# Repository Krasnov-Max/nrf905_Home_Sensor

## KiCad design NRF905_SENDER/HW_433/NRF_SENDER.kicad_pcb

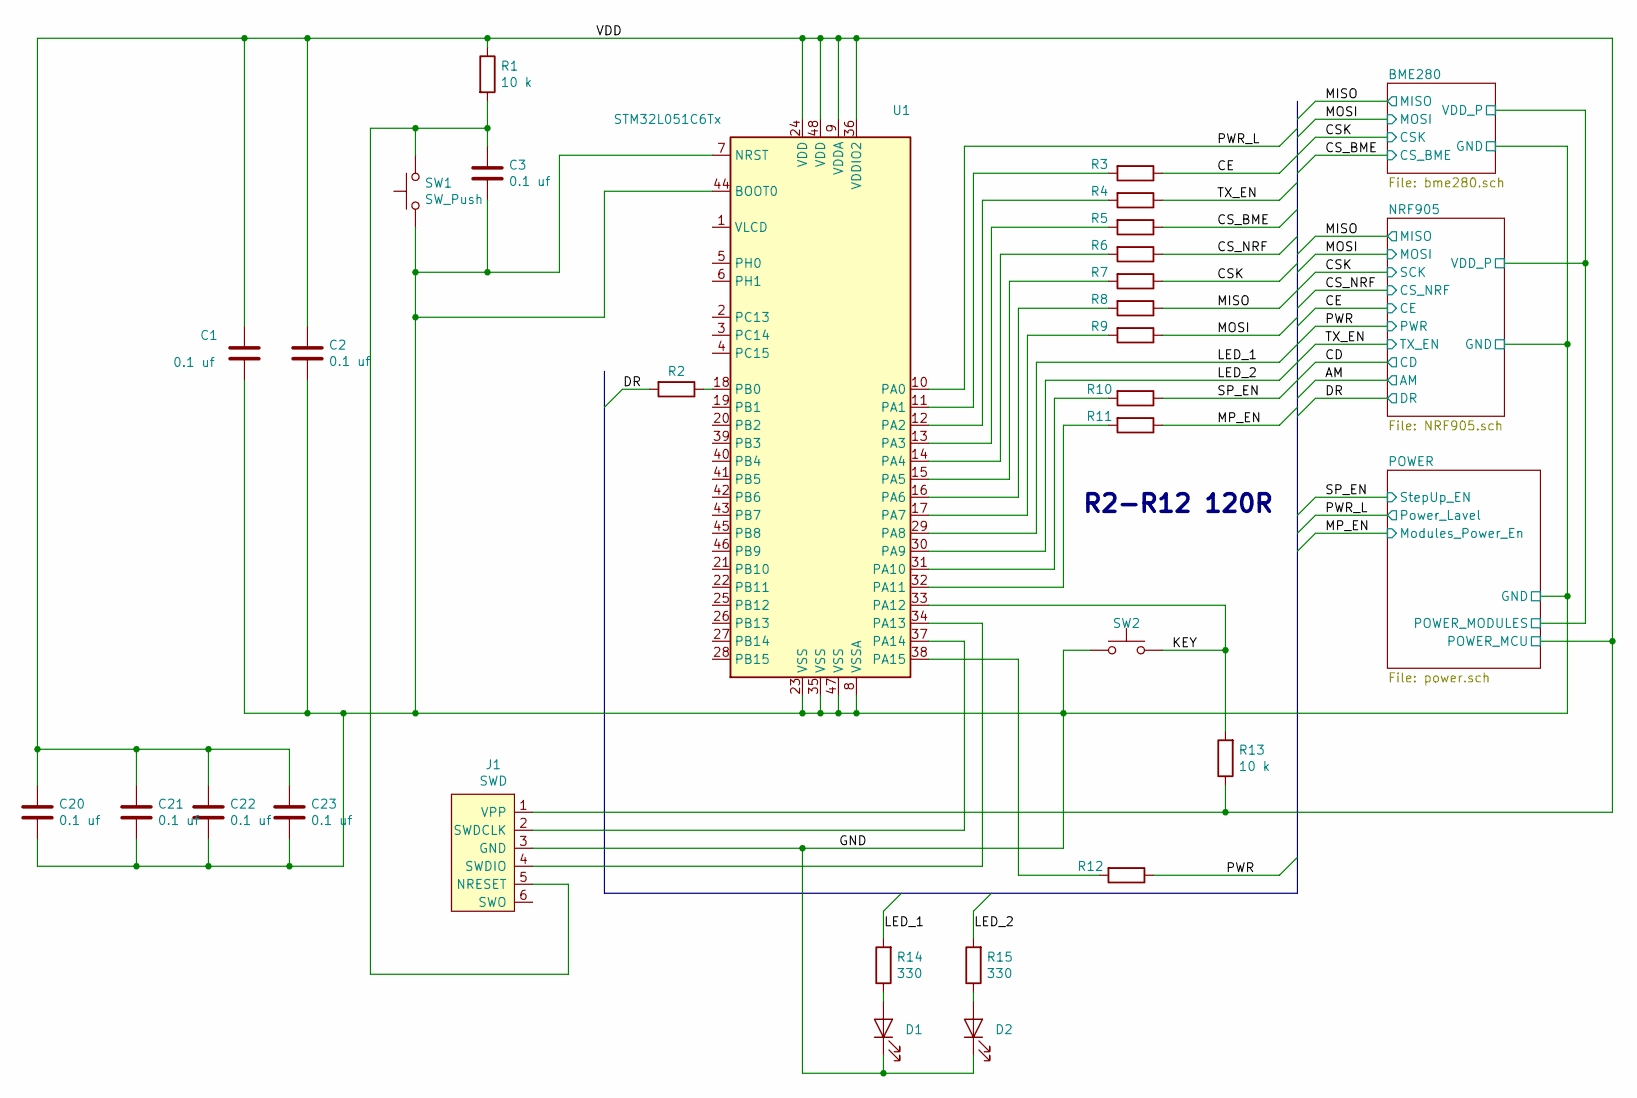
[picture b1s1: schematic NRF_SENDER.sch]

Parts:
C1, C2, C3, C20, C21, C22, C23: 0.1 uf; C_0603_1608Metric_Pad1.05x0.95mm_HandSolder
D1, D2: LED; LED_0603_1608Metric_Pad1.05x0.95mm_HandSolder
J1: SWD; PinHeader_1x06_P2.54mm_Vertical
R1, R13: 10 k; R_0603_1608Metric_Pad1.05x0.95mm_HandSolder
R2, R3, R4, R5, R6, R7, R8, R9, R10, R11, R12: 120; R_0603_1608Metric_Pad1.05x0.95mm_HandSolder
R14, R15: 330; R_0603_1608Metric_Pad1.05x0.95mm_HandSolder
SW1, SW2: SW_Push; SW_SPST_EVQP2
U1: STM32L051C6Tx; LQFP-48_7x7mm_P0.5mm

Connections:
/CE: R3.1; also elsewhere on the board
/CSK: R7.1; also elsewhere on the board
/CS_BME: R5.1; also elsewhere on the board
/CS_NRF: R6.1; also elsewhere on the board
/DR: R2.2; also elsewhere on the board
/KEY: R13.2, SW2.2, U1.33 (PA12)
/LED_1: R14.2, U1.29 (PA8)
/LED_2: R15.2, U1.30 (PA9)
/MISO: R8.1; also elsewhere on the board
/MOSI: R9.1; also elsewhere on the board
/MP_EN: R11.1; also elsewhere on the board
/PWR: R12.1; also elsewhere on the board
/PWR_L: U1.10 (PA0); also elsewhere on the board
/SP_EN: R10.1; also elsewhere on the board
/TX_EN: R4.1; also elsewhere on the board
/VDD: C1.1, C2.1, C20.1, C21.1, C22.1, C23.1, J1.1 (VPP), R1.1, R13.1, U1.9 (VDDA), U1.24 (VDD), U1.36 (VDDIO2), U1.48 (VDD); also elsewhere on the board
GND: C1.2, C2.2, C3.2, C20.2, C21.2, C22.2, C23.2, D1.1 (K), D2.1 (K), J1.3 (GND), SW1.1, SW2.1, U1.7 (NRST), U1.8 (VSSA), U1.23 (VSS), U1.35 (VSS), U1.44 (BOOT0), U1.47 (VSS); also elsewhere on the board
unnamed: C3.1, J1.5 (NRESET), R1.2, SW1.2
unnamed: D1.2 (A), R14.1
unnamed: D2.2 (A), R15.1
unnamed: J1.2 (SWDCLK), U1.37 (PA14)
unnamed: J1.4 (SWDIO), U1.34 (PA13)
unnamed: R2.1, U1.18 (PB0)
unnamed: R3.2, U1.11 (PA1)
unnamed: R4.2, U1.12 (PA2)
unnamed: R5.2, U1.13 (PA3)
unnamed: R6.2, U1.14 (PA4)
unnamed: R7.2, U1.15 (PA5)
unnamed: R8.2, U1.16 (PA6)
unnamed: R9.2, U1.17 (PA7)
unnamed: R10.2, U1.31 (PA10)
unnamed: R11.2, U1.32 (PA11)
unnamed: R12.2, U1.38 (PA15)

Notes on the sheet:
R2-R12 120R

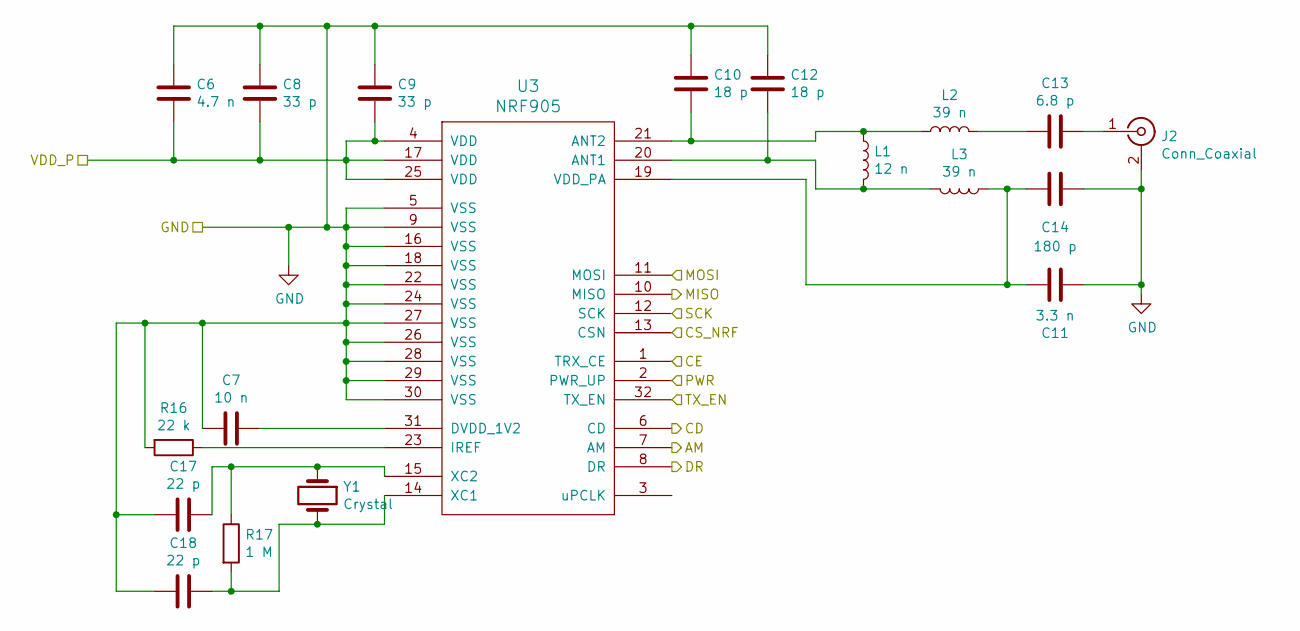
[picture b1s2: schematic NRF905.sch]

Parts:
C6: 4.7 n; C_0402_1005Metric
C7: 10 n; C_0402_1005Metric
C8, C9: 33 p; C_0402_1005Metric
C10, C12: 18 p; C_0402_1005Metric
C11: 3.3 n; C_0402_1005Metric
C13: 6.8 p; C_0402_1005Metric
C14: 180 p; C_0402_1005Metric
C17, C18: 22 p; C_0402_1005Metric
J2: Conn_Coaxial; U.FL_Molex_MCRF_73412-0110_Vertical
L1: 12 n; L_0402_1005Metric
L2, L3: 39 n; L_0402_1005Metric
R16: 22 k; R_0603_1608Metric_Pad1.05x0.95mm_HandSolder
R17: 1 M; R_0402_1005Metric
U3: NRF905; QFN-32-1EP_5x5mm_P0.5mm_EP3.6x3.6mm
Y1: Crystal; Crystal_SMD_TXC_7A-2Pin_5x3.2mm

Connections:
/CE: U3.1 (TRX_CE); also elsewhere on the board
/CSK: U3.12 (SCK); also elsewhere on the board
/CS_NRF: U3.13 (CSN); also elsewhere on the board
/DR: U3.8 (DR); also elsewhere on the board
/MISO: U3.10 (MISO); also elsewhere on the board
/MOSI: U3.11 (MOSI); also elsewhere on the board
/POWER/POWER_MODULES: C6.2, C8.2, C9.2, U3.4 (VDD), U3.17 (VDD), U3.25 (VDD); also elsewhere on the board
/PWR: U3.2 (PWR_UP); also elsewhere on the board
/TX_EN: U3.32 (TX_EN); also elsewhere on the board
GND: C6.1, C7.2, C8.1, C9.1, C10.1, C11.2, C12.1, C14.1, C17.2, C18.2, J2.2 (Ext), R16.2, U3.5 (VSS), U3.9 (VSS), U3.16 (VSS), U3.18 (VSS), U3.22 (VSS), U3.24 (VSS), U3.26 (VSS), U3.27 (VSS), U3.28 (VSS), U3.29 (VSS), U3.30 (VSS), U3.33; also elsewhere on the board
unnamed: C7.1, U3.31 (DVDD_1V2)
unnamed: C10.2, L1.1, L2.1, U3.21 (ANT2)
unnamed: C11.1, C14.2, L3.1, U3.19 (VDD_PA)
unnamed: C12.2, L1.2, L3.2, U3.20 (ANT1)
unnamed: C13.1, J2.1 (In)
unnamed: C13.2, L2.2
unnamed: C17.1, R17.1, U3.15 (XC2), Y1.1
unnamed: C18.1, R17.2, U3.14 (XC1), Y1.2
unnamed: R16.1, U3.23 (IREF)

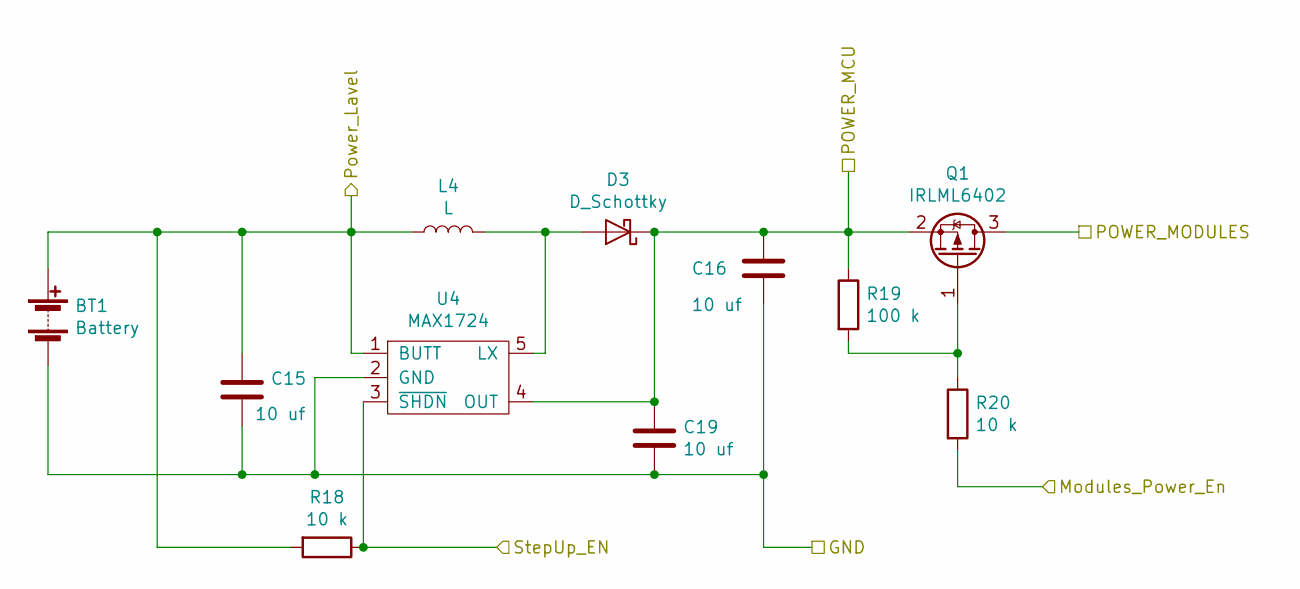
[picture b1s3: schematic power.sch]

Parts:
BT1: Battery; CR14250
C15, C16, C19: 10 uf; C_0603_1608Metric
D3: D_Schottky; D_SOD-123F
L4: L; L_Bourns-SRN8040_8x8.15mm
Q1: IRLML6402; SOT-23
R18, R20: 10 k; R_0603_1608Metric_Pad1.05x0.95mm_HandSolder
R19: 100 k; R_0603_1608Metric_Pad1.05x0.95mm_HandSolder
U4: MAX1724; TSOT

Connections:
/MP_EN: R20.2; also elsewhere on the board
/POWER/POWER_MODULES: Q1.3 (D); also elsewhere on the board
/PWR_L: BT1.1 (+), C15.1, L4.1, R18.2, U4.1 (BUTT); also elsewhere on the board
/SP_EN: R18.1, U4.3 (~SHDN); also elsewhere on the board
/VDD: C16.1, C19.1, D3.1 (K), Q1.2 (S), R19.1, U4.4 (OUT); also elsewhere on the board
GND: BT1.2 (-), C15.2, C16.2, C19.2, U4.2 (GND); also elsewhere on the board
unnamed: D3.2 (A), L4.2, U4.5 (LX)
unnamed: Q1.1 (G), R19.2, R20.1

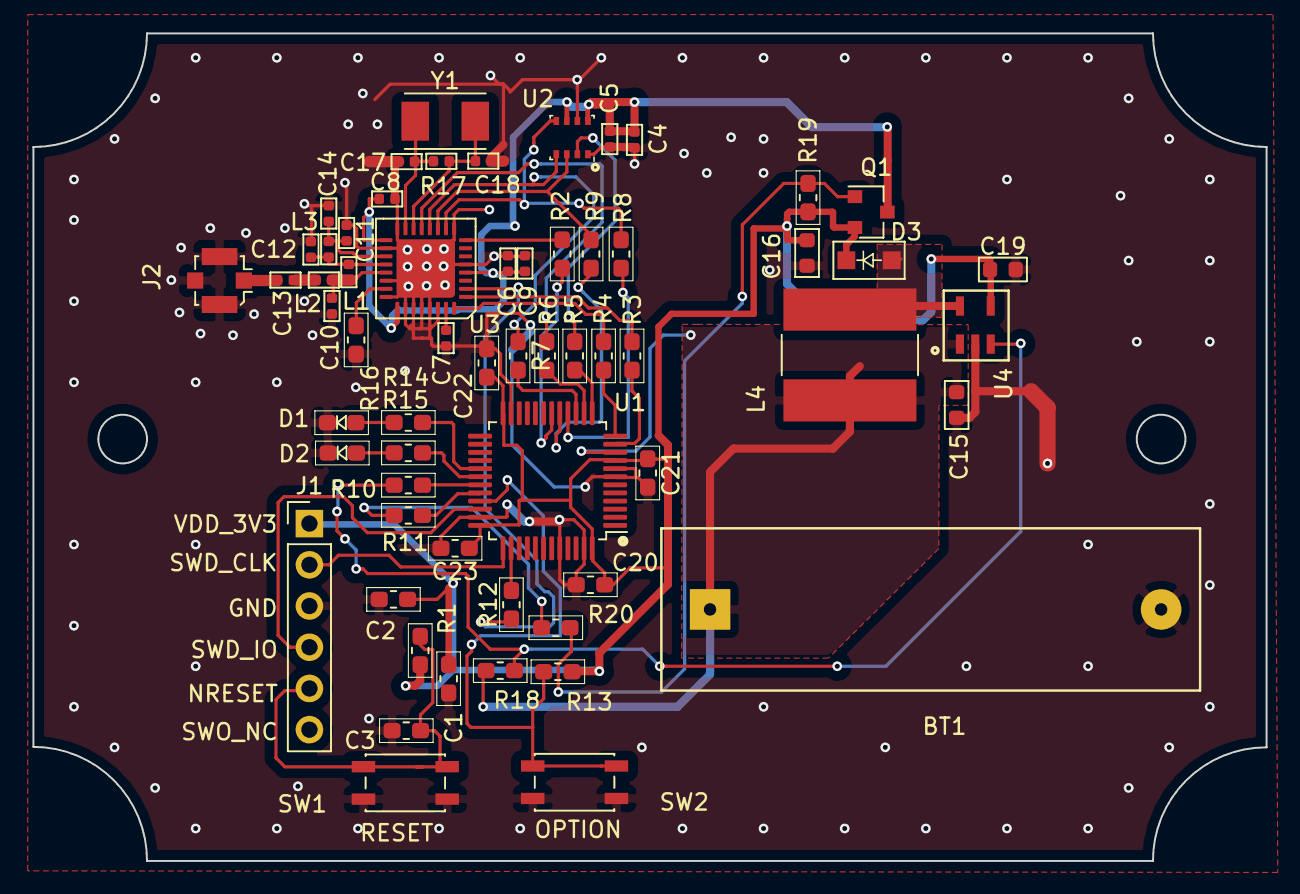
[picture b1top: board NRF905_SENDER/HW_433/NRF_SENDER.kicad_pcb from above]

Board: 2 copper layers, 76.0 x 51.0 mm, 61 parts (0 on the bottom side), 45 nets.

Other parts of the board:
C4: 0.1 uf; C_0402_1005Metric
C5: 4.7 uf; C_0402_1005Metric
U2: BME280; Bosch_LGA-8_2.5x2.5mm_P0.65mm_ClockwisePinNumbering

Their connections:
/CSK: U2.4; also elsewhere on the board
/CS_BME: U2.2; also elsewhere on the board
/MISO: U2.5; also elsewhere on the board
/MOSI: U2.3; also elsewhere on the board
/POWER/POWER_MODULES: C4.1, C5.1, U2.6, U2.8; also elsewhere on the board
GND: C4.2, C5.2, U2.1, U2.7; also elsewhere on the board

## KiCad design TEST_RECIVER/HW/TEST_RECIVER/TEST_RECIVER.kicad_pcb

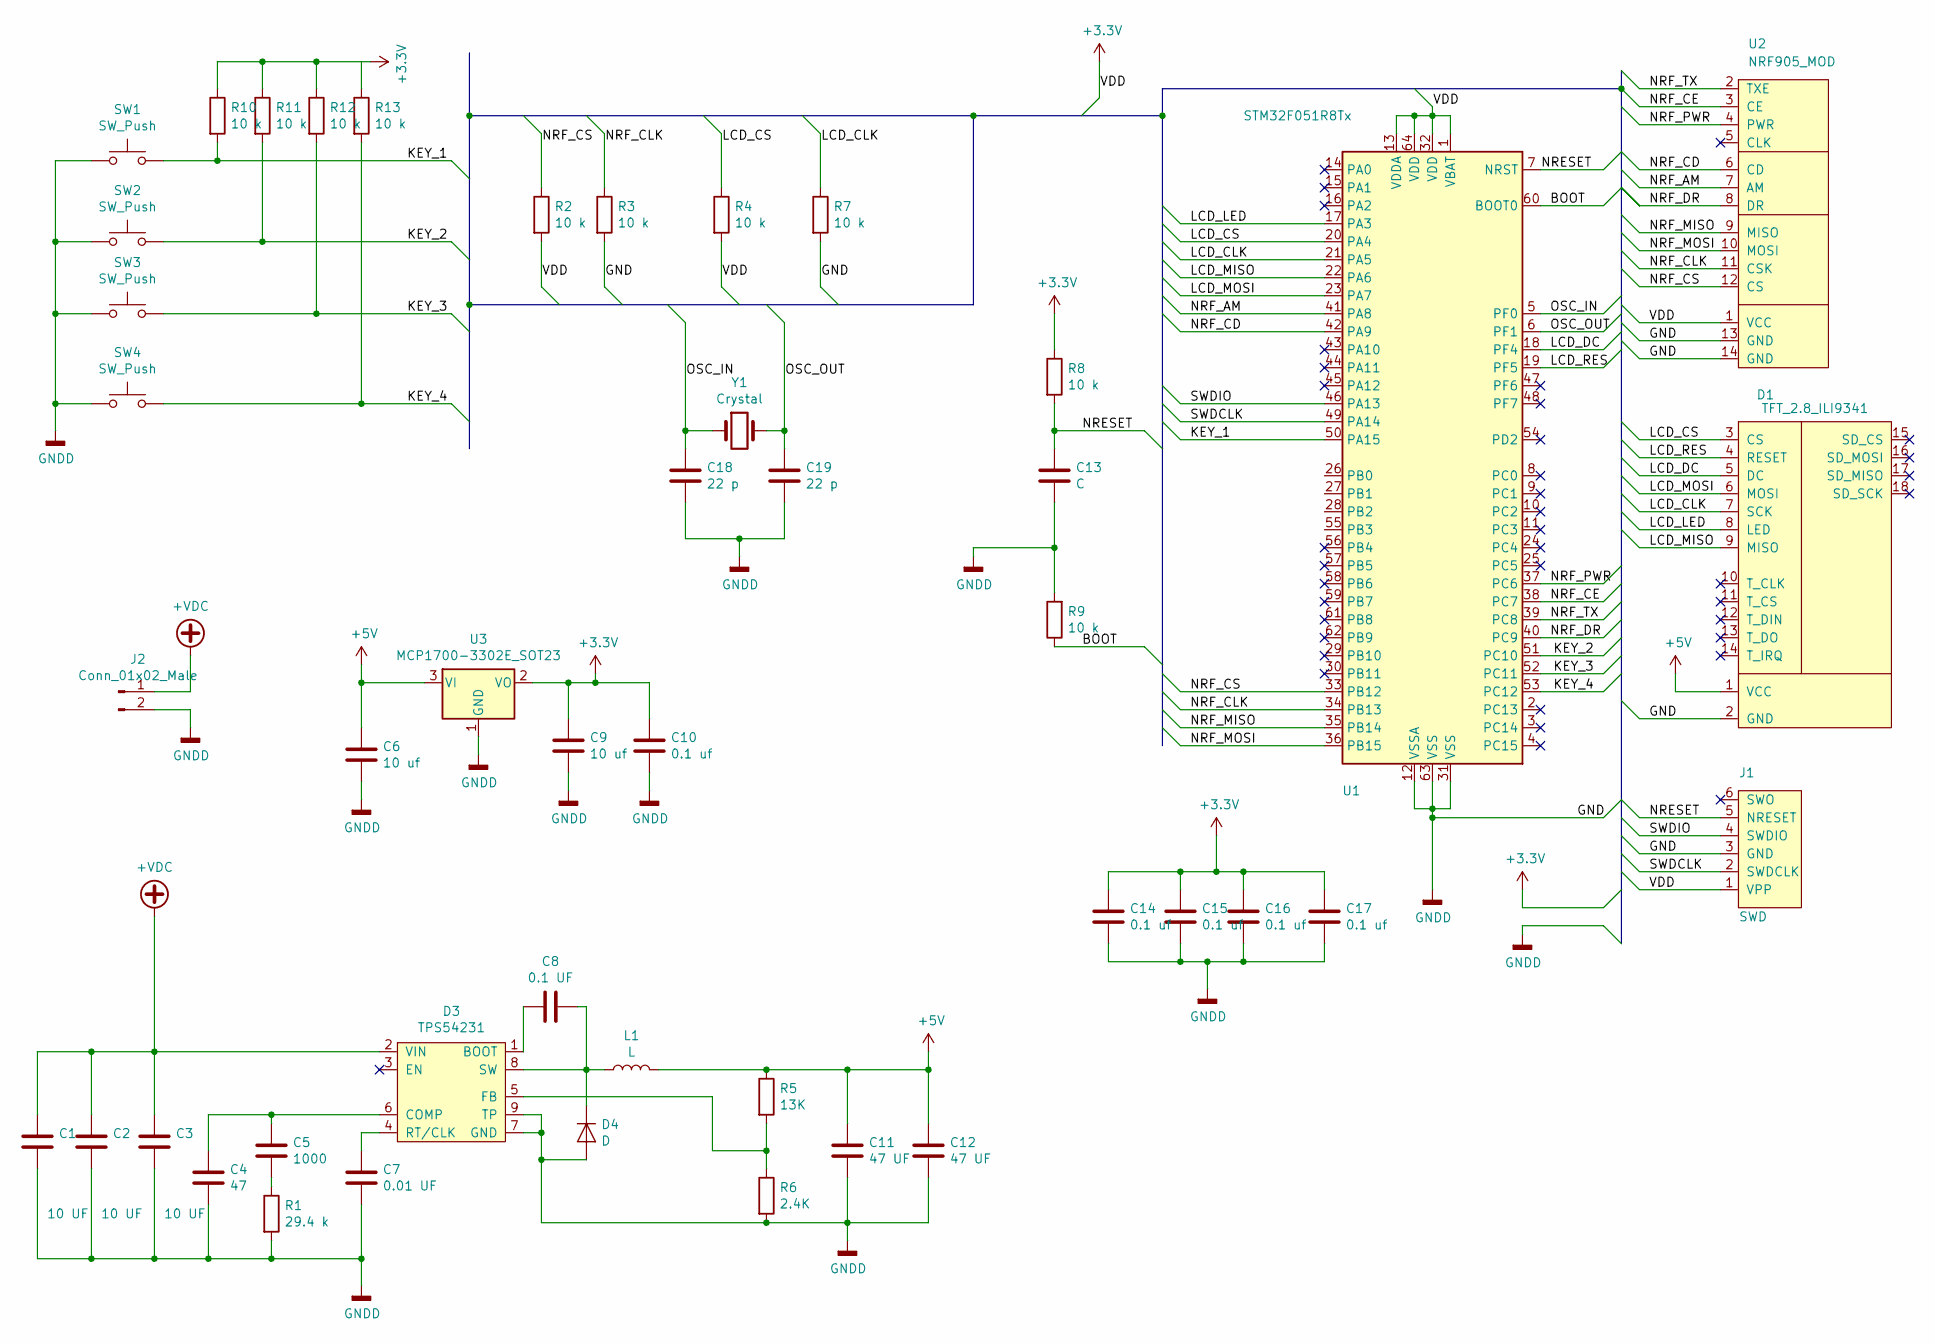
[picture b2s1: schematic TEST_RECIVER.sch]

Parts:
C1, C2, C3: 10 UF; C_1210_3225Metric_Pad1.42x2.65mm_HandSolder
C4: 47; C_0805_2012Metric_Pad1.15x1.40mm_HandSolder
C5: 1000; C_0805_2012Metric_Pad1.15x1.40mm_HandSolder
C6, C9: 10 uf; C_0805_2012Metric_Pad1.15x1.40mm_HandSolder
C7: 0.01 UF; C_0805_2012Metric_Pad1.15x1.40mm_HandSolder
C8: 0.1 UF; C_0805_2012Metric_Pad1.15x1.40mm_HandSolder
C10, C14, C15, C16, C17: 0.1 uf; C_0805_2012Metric_Pad1.15x1.40mm_HandSolder
C11, C12: 47 UF; C_1206_3216Metric_Pad1.42x1.75mm_HandSolder
C13: C; C_0805_2012Metric_Pad1.15x1.40mm_HandSolder
C18, C19: 22 p; C_0805_2012Metric_Pad1.15x1.40mm_HandSolder
D1: TFT_2.8_ILI9341; TFT_2_8_ILI9431
D3: TPS54231; Texas_R-PDSO-G8_EP2.95x4.9mm_Mask2.4x3.1mm
D4: D; D_SOD-123F
J1: SWD; PinHeader_1x06_P2.54mm_Vertical
J2: Conn_01x02_Male; PinSocket_1x02_P2.54mm_Vertical
L1: L; L_Bourns_SRR1260
R1: 29.4 k; R_0805_2012Metric_Pad1.15x1.40mm_HandSolder
R2, R3, R4, R7, R8, R9, R10, R11, R12, R13: 10 k; R_0805_2012Metric_Pad1.15x1.40mm_HandSolder
R5: 13K; R_0805_2012Metric_Pad1.15x1.40mm_HandSolder
R6: 2.4K; R_0805_2012Metric_Pad1.15x1.40mm_HandSolder
SW1, SW2, SW3, SW4: SW_Push; SW_PUSH_6mm
U1: STM32F051R8Tx; LQFP-64_10x10mm_P0.5mm
U2: NRF905_MOD; PinSocket_2x07_P2.54mm_Vertical
U3: MCP1700-3302E_SOT23; SOT-23
Y1: Crystal; Crystal_SMD_5032-2Pin_5.0x3.2mm_HandSoldering

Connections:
+3V3: C9.1, C10.1, C14.1, C15.1, C16.1, C17.1, J1.1 (VPP), R2.2, R4.2, R8.1, R10.1, R11.1, R12.1, R13.1, U1.1 (VBAT), U1.13 (VDDA), U1.32 (VDD), U1.64 (VDD), U2.1 (VCC), U3.2 (VO)
+5V: C6.1, C11.1, C12.1, D1.1 (VCC), L1.2, R5.1, U3.3 (VI)
+VDC: C1.1, C2.1, C3.1, D3.2 (VIN), J2.1
/BOOT: R9.1, U1.60 (BOOT0)
/KEY_1: R10.2, SW1.2, U1.50 (PA15)
/KEY_2: R11.2, SW2.2, U1.51 (PC10)
/KEY_3: R12.2, SW3.2, U1.52 (PC11)
/KEY_4: R13.2, SW4.2, U1.53 (PC12)
/LCD_CLK: D1.7 (SCK), R7.1, U1.21 (PA5)
/LCD_CS: D1.3 (CS), R4.1, U1.20 (PA4)
/LCD_DC: D1.5 (DC), U1.18 (PF4)
/LCD_LED: D1.8 (LED), U1.17 (PA3)
/LCD_MISO: D1.9 (MISO), U1.22 (PA6)
/LCD_MOSI: D1.6 (MOSI), U1.23 (PA7)
/LCD_RES: D1.4 (RESET), U1.19 (PF5)
/NRESET: C13.1, J1.5 (NRESET), R8.2, U1.7 (NRST)
/NRF_AM: U1.41 (PA8), U2.7 (AM)
/NRF_CD: U1.42 (PA9), U2.6 (CD)
/NRF_CE: U1.38 (PC7), U2.3 (CE)
/NRF_CLK: R3.1, U1.34 (PB13), U2.11 (CSK)
/NRF_CS: R2.1, U1.33 (PB12), U2.12 (CS)
/NRF_DR: U1.40 (PC9), U2.8 (DR)
/NRF_MISO: U1.35 (PB14), U2.9 (MISO)
/NRF_MOSI: U1.36 (PB15), U2.10 (MOSI)
/NRF_PWR: U1.37 (PC6), U2.4 (PWR)
/NRF_TX: U1.39 (PC8), U2.2 (TXE)
/OSC_IN: C18.1, U1.5 (PF0), Y1.1
/OSC_OUT: C19.1, U1.6 (PF1), Y1.2
/SWDCLK: J1.2 (SWDCLK), U1.49 (PA14)
/SWDIO: J1.4 (SWDIO), U1.46 (PA13)
GNDD: C1.2, C2.2, C3.2, C4.2, C6.2, C7.2, C9.2, C10.2, C11.2, C12.2, C13.2, C14.2, C15.2, C16.2, C17.2, C18.2, C19.2, D1.2 (GND), D3.7 (GND), D3.9 (TP), D4.2 (A), J1.3 (GND), J2.2, R1.2, R3.2, R6.2, R7.2, R9.2, SW1.1, SW2.1, SW3.1, SW4.1, U1.12 (VSSA), U1.31 (VSS), U1.63 (VSS), U2.13 (GND), U2.14 (GND), U3.1 (GND)
unnamed: C4.1, C5.1, D3.6 (COMP)
unnamed: C5.2, R1.1
unnamed: C7.1, D3.4 (RT/CLK)
unnamed: C8.1, D3.8 (SW), D4.1 (K), L1.1
unnamed: C8.2, D3.1 (BOOT)
unnamed: D3.5 (FB), R5.2, R6.1

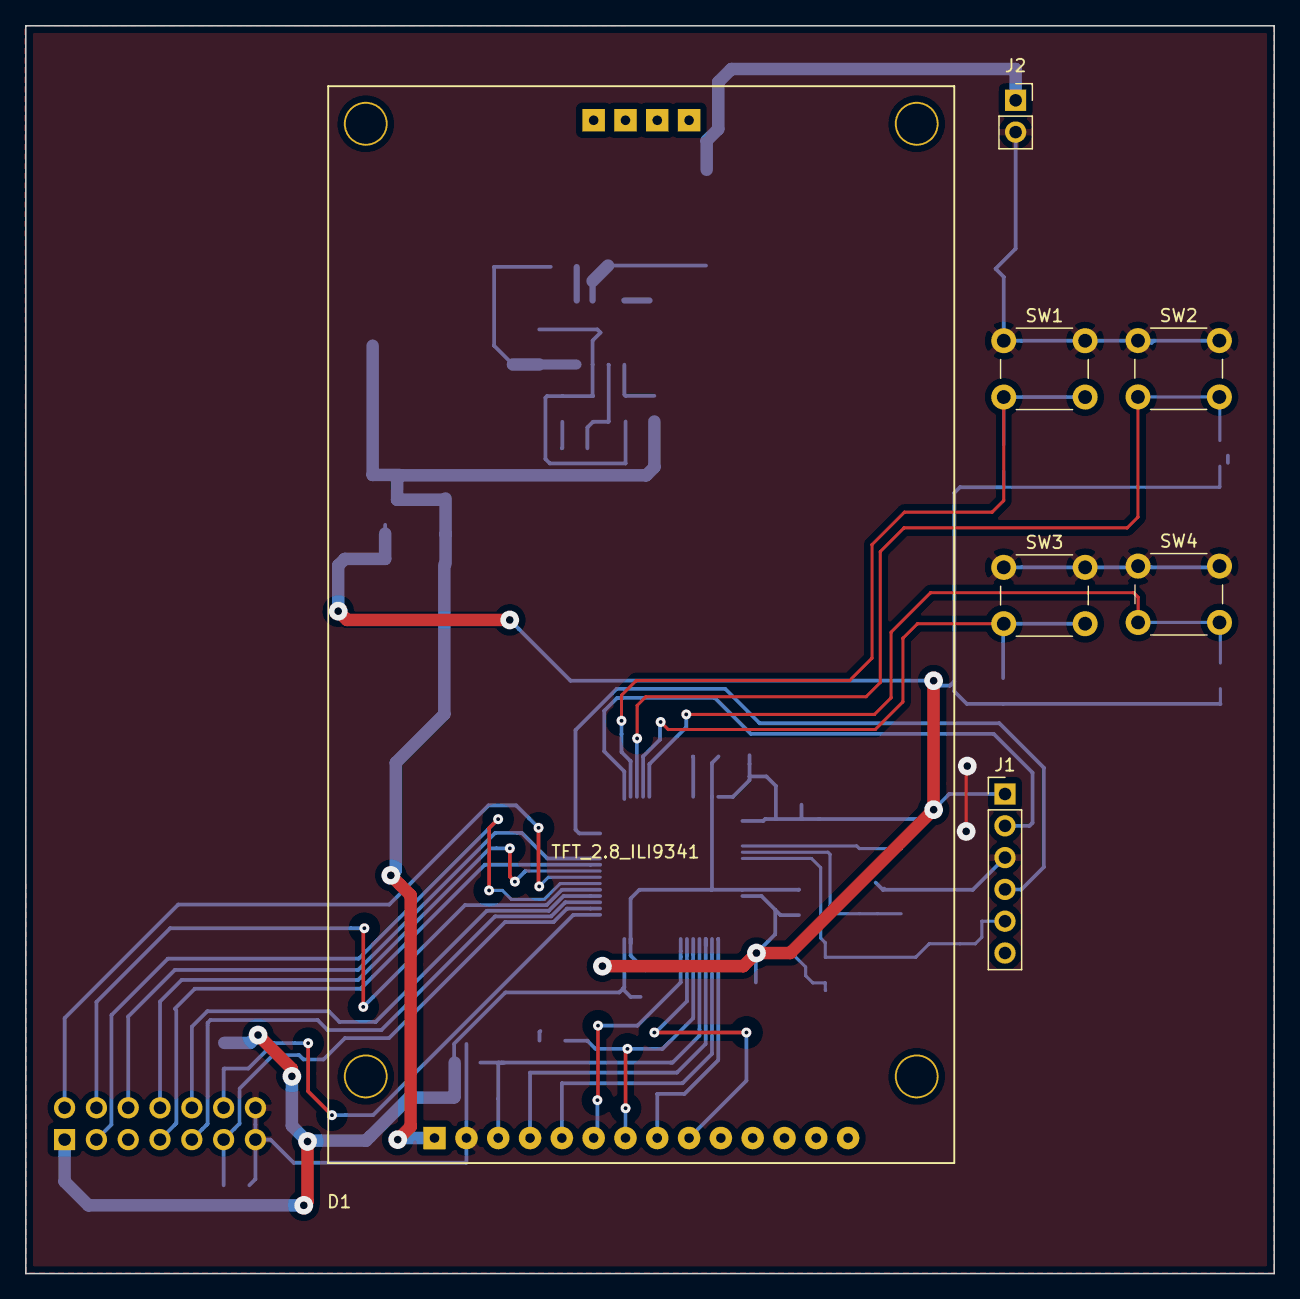
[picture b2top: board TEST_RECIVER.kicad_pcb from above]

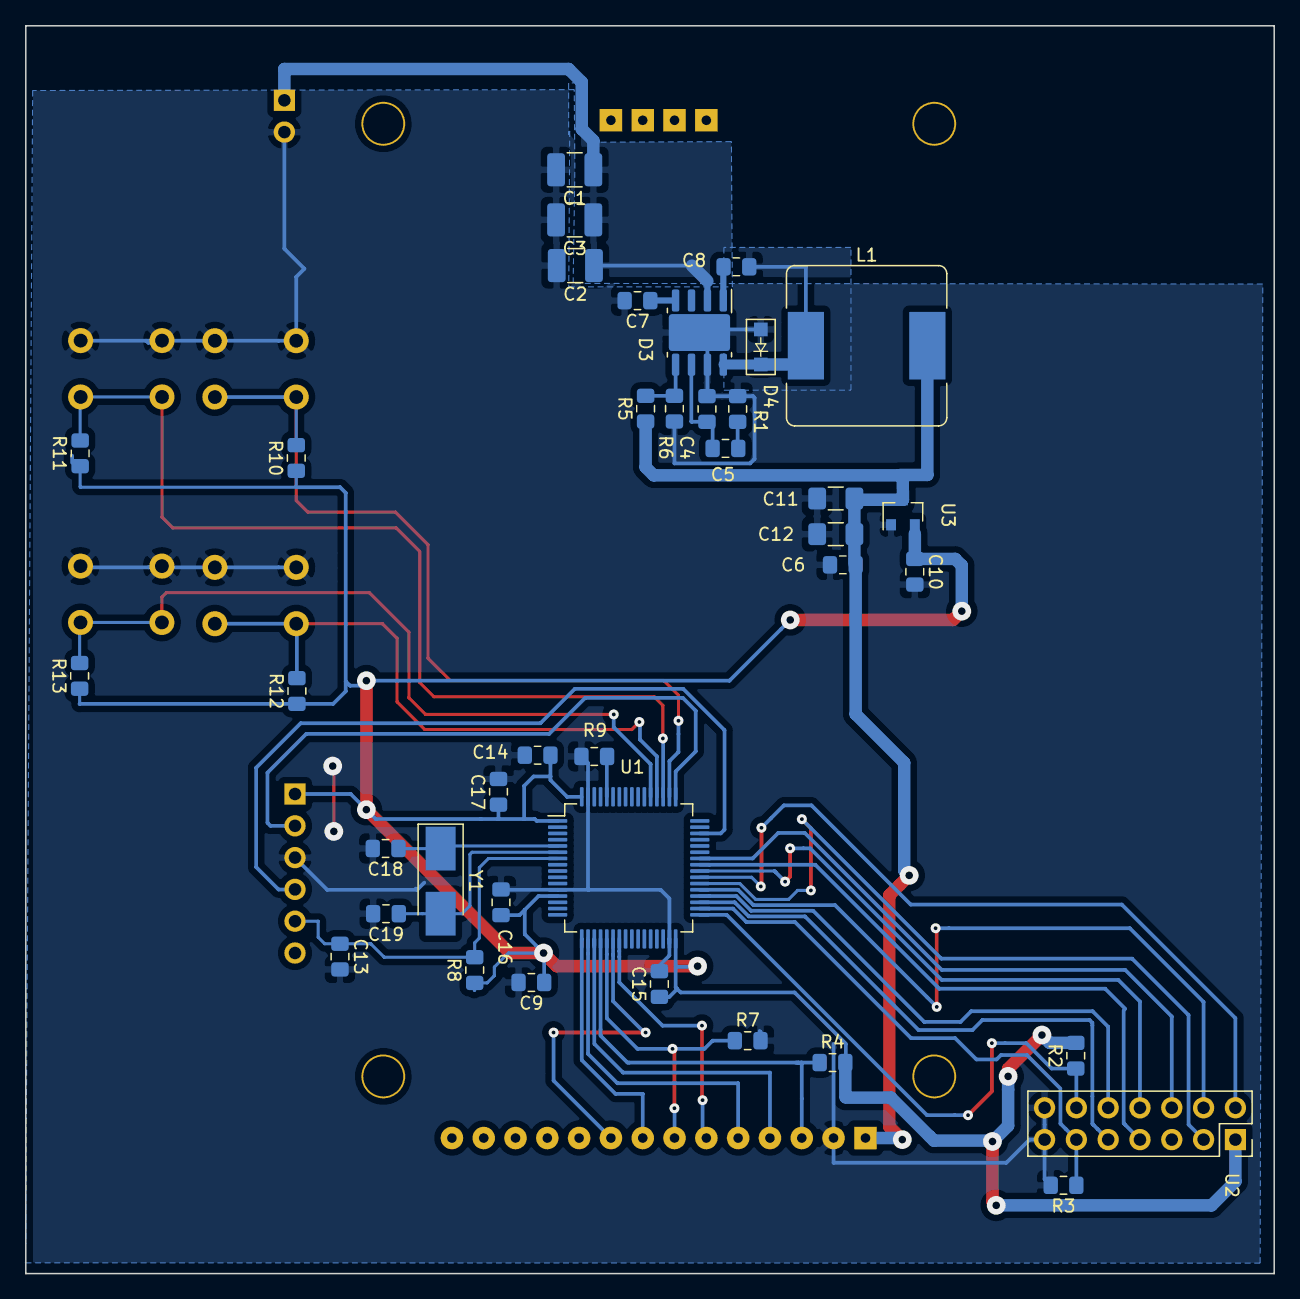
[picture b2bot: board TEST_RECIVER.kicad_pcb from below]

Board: 2 copper layers, 99.7 x 99.7 mm, 46 parts (39 on the bottom side), 37 nets.

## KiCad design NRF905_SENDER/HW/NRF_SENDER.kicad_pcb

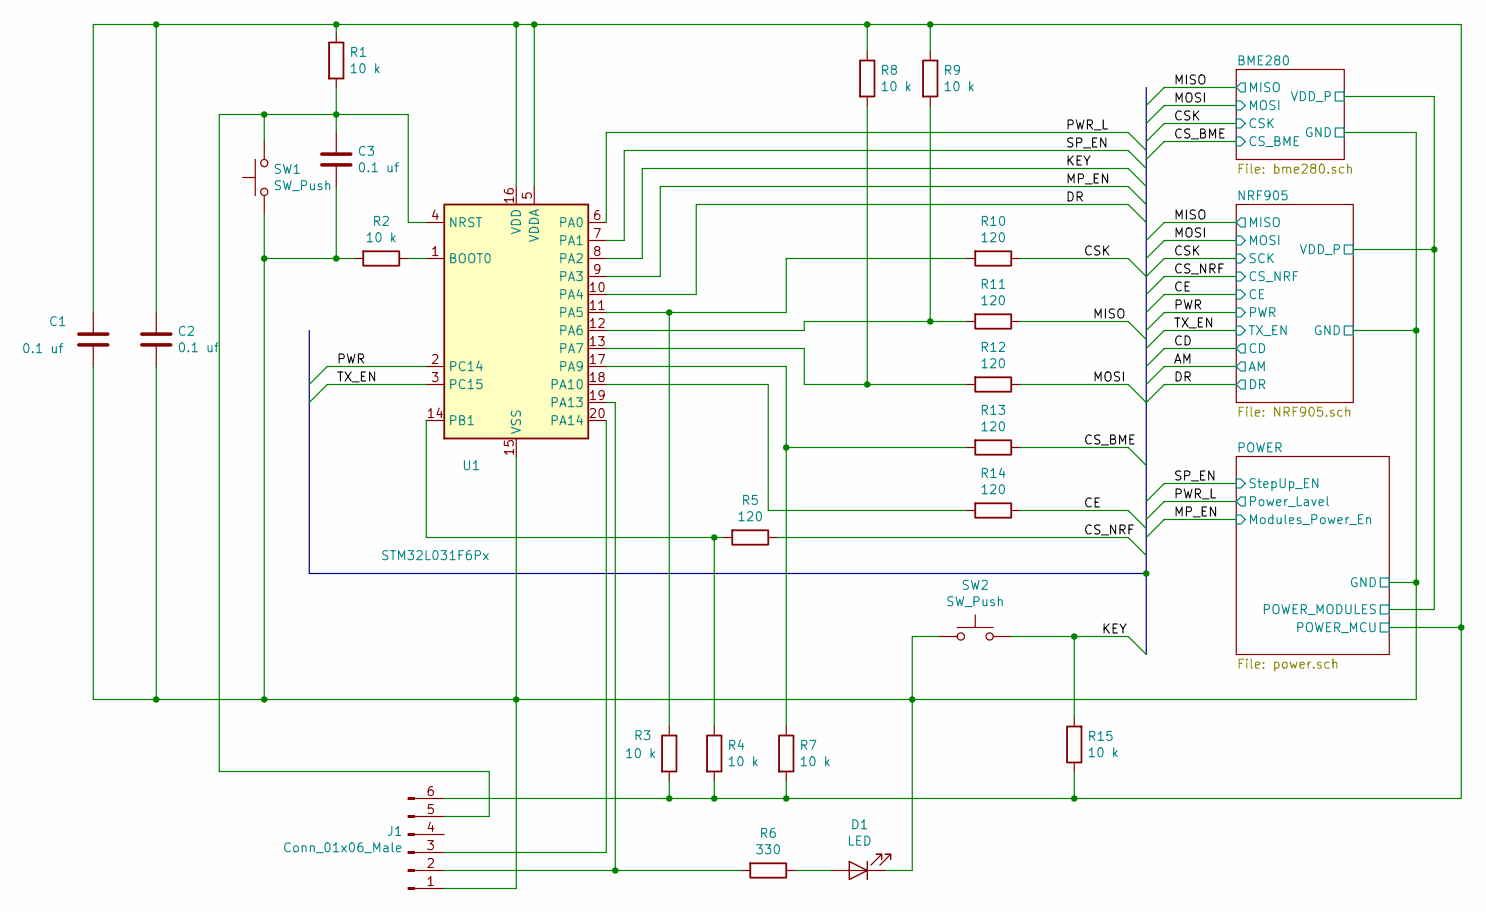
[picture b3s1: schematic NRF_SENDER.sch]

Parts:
C1, C2, C3: 0.1 uf; C_0402_1005Metric
D1: LED; LED_0603_1608Metric
J1: Conn_01x06_Male; PinSocket_1x06_P2.54mm_Vertical
R1, R2, R3, R4, R7, R8, R9, R15: 10 k; R_0402_1005Metric
R5, R10, R11, R12, R13, R14: 120; R_0402_1005Metric
R6: 330; R_0402_1005Metric
SW1, SW2: SW_Push; SW_SPST_EVQP2
U1: STM32L031F6Px; TSSOP-20_4.4x6.5mm_P0.65mm

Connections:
/CE: R14.1; also elsewhere on the board
/CSK: R10.1; also elsewhere on the board
/CS_BME: R13.1; also elsewhere on the board
/CS_NRF: R5.1; also elsewhere on the board
/DR: U1.10 (PA4); also elsewhere on the board
/KEY: R15.2, SW2.2, U1.8 (PA2)
/MISO: R11.1; also elsewhere on the board
/MOSI: R12.1; also elsewhere on the board
/MP_EN: U1.9 (PA3); also elsewhere on the board
/POWER/POWER_MCU: C1.1, C2.1, J1.6, R1.1, R3.2, R4.2, R7.2, R8.1, R9.1, R15.1, U1.5 (VDDA), U1.16 (VDD); also elsewhere on the board
/PWR: U1.2 (PC14); also elsewhere on the board
/PWR_L: U1.6 (PA0); also elsewhere on the board
/SP_EN: U1.7 (PA1); also elsewhere on the board
/TX_EN: U1.3 (PC15); also elsewhere on the board
GND: C1.2, C2.2, C3.2, D1.1 (K), J1.1, R2.2, SW1.1, SW2.1, U1.15 (VSS); also elsewhere on the board
unnamed: C3.1, J1.5, R1.2, SW1.2, U1.4 (NRST)
unnamed: D1.2 (A), R6.1
unnamed: J1.2, R6.2, U1.19 (PA13)
unnamed: J1.3, U1.20 (PA14)
unnamed: R2.1, U1.1 (BOOT0)
unnamed: R4.1, R5.2, U1.14 (PB1)
unnamed: R3.1, R10.2, U1.11 (PA5)
unnamed: R9.2, R11.2, U1.12 (PA6)
unnamed: R8.2, R12.2, U1.13 (PA7)
unnamed: R7.1, R13.2, U1.17 (PA9)
unnamed: R14.2, U1.18 (PA10)

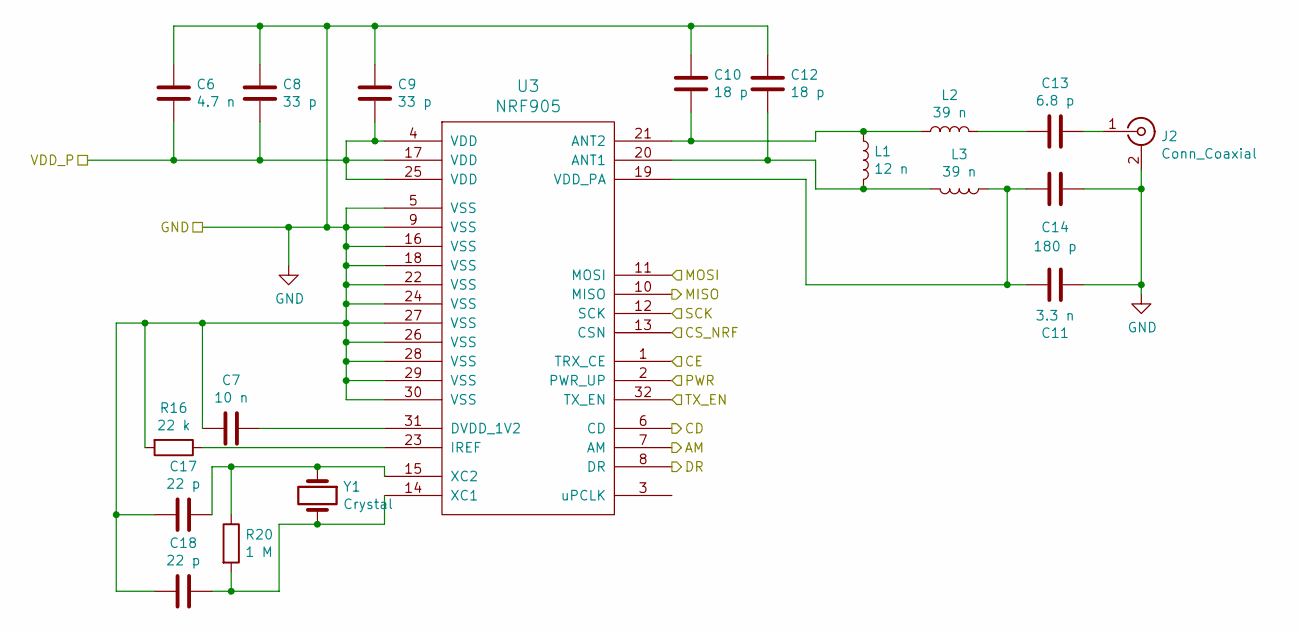
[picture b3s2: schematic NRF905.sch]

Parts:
C6: 4.7 n; C_0402_1005Metric
C7: 10 n; C_0402_1005Metric
C8, C9: 33 p; C_0402_1005Metric
C10, C12: 18 p; C_0402_1005Metric
C11: 3.3 n; C_0402_1005Metric
C13: 6.8 p; C_0402_1005Metric
C14: 180 p; C_0402_1005Metric
C17, C18: 22 p; C_0402_1005Metric
J2: Conn_Coaxial; U.FL_Molex_MCRF_73412-0110_Vertical
L1: 12 n; L_0402_1005Metric
L2, L3: 39 n; L_0402_1005Metric
R16: 22 k; R_0402_1005Metric
R20: 1 M; R_0402_1005Metric
U3: NRF905; QFN-32-1EP_5x5mm_P0.5mm_EP3.6x3.6mm
Y1: Crystal; Crystal_SMD_TXC_7A-2Pin_5x3.2mm

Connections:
/CE: U3.1 (TRX_CE); also elsewhere on the board
/CSK: U3.12 (SCK); also elsewhere on the board
/CS_NRF: U3.13 (CSN); also elsewhere on the board
/DR: U3.8 (DR); also elsewhere on the board
/MISO: U3.10 (MISO); also elsewhere on the board
/MOSI: U3.11 (MOSI); also elsewhere on the board
/POWER/POWER_MODULES: C6.2, C8.2, C9.2, U3.4 (VDD), U3.17 (VDD), U3.25 (VDD); also elsewhere on the board
/PWR: U3.2 (PWR_UP); also elsewhere on the board
/TX_EN: U3.32 (TX_EN); also elsewhere on the board
GND: C6.1, C7.2, C8.1, C9.1, C10.1, C11.2, C12.1, C14.1, C17.2, C18.2, J2.2 (Ext), R16.2, U3.5 (VSS), U3.9 (VSS), U3.16 (VSS), U3.18 (VSS), U3.22 (VSS), U3.24 (VSS), U3.26 (VSS), U3.27 (VSS), U3.28 (VSS), U3.29 (VSS), U3.30 (VSS), U3.33; also elsewhere on the board
unnamed: C7.1, U3.31 (DVDD_1V2)
unnamed: C10.2, L1.1, L2.1, U3.21 (ANT2)
unnamed: C11.1, C14.2, L3.1, U3.19 (VDD_PA)
unnamed: C12.2, L1.2, L3.2, U3.20 (ANT1)
unnamed: C13.1, J2.1 (In)
unnamed: C13.2, L2.2
unnamed: C17.1, R20.1, U3.15 (XC2), Y1.1
unnamed: C18.1, R20.2, U3.14 (XC1), Y1.2
unnamed: R16.1, U3.23 (IREF)

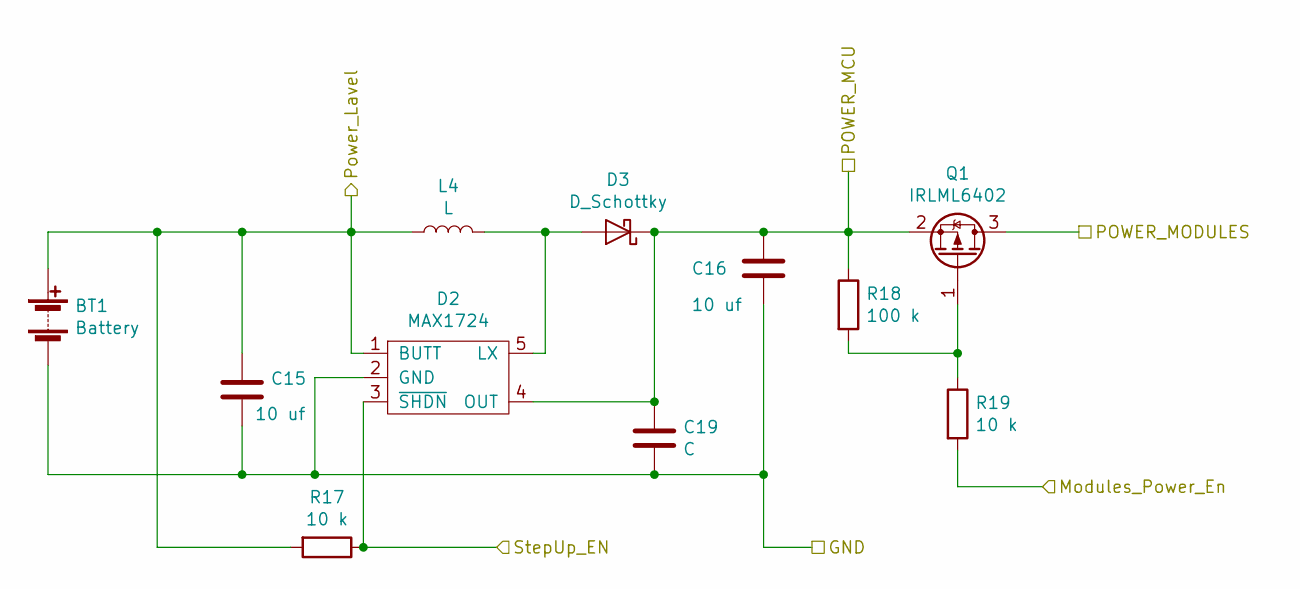
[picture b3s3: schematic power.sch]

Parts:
BT1: Battery; CR14250
C15, C16: 10 uf; C_0603_1608Metric
C19: C; C_0603_1608Metric
D2: MAX1724; TSOT
D3: D_Schottky; D_SOD-123F
L4: L; L_Bourns-SRN8040_8x8.15mm
Q1: IRLML6402; SOT-23
R17, R19: 10 k; R_0402_1005Metric
R18: 100 k; R_0402_1005Metric

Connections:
/MP_EN: R19.2; also elsewhere on the board
/POWER/POWER_MCU: C16.1, C19.1, D2.4 (OUT), D3.1 (K), Q1.2 (S), R18.1; also elsewhere on the board
/POWER/POWER_MODULES: Q1.3 (D); also elsewhere on the board
/PWR_L: BT1.1 (+), C15.1, D2.1 (BUTT), L4.1, R17.2; also elsewhere on the board
/SP_EN: D2.3 (~SHDN), R17.1; also elsewhere on the board
GND: BT1.2 (-), C15.2, C16.2, C19.2, D2.2 (GND); also elsewhere on the board
unnamed: D2.5 (LX), D3.2 (A), L4.2
unnamed: Q1.1 (G), R18.2, R19.1

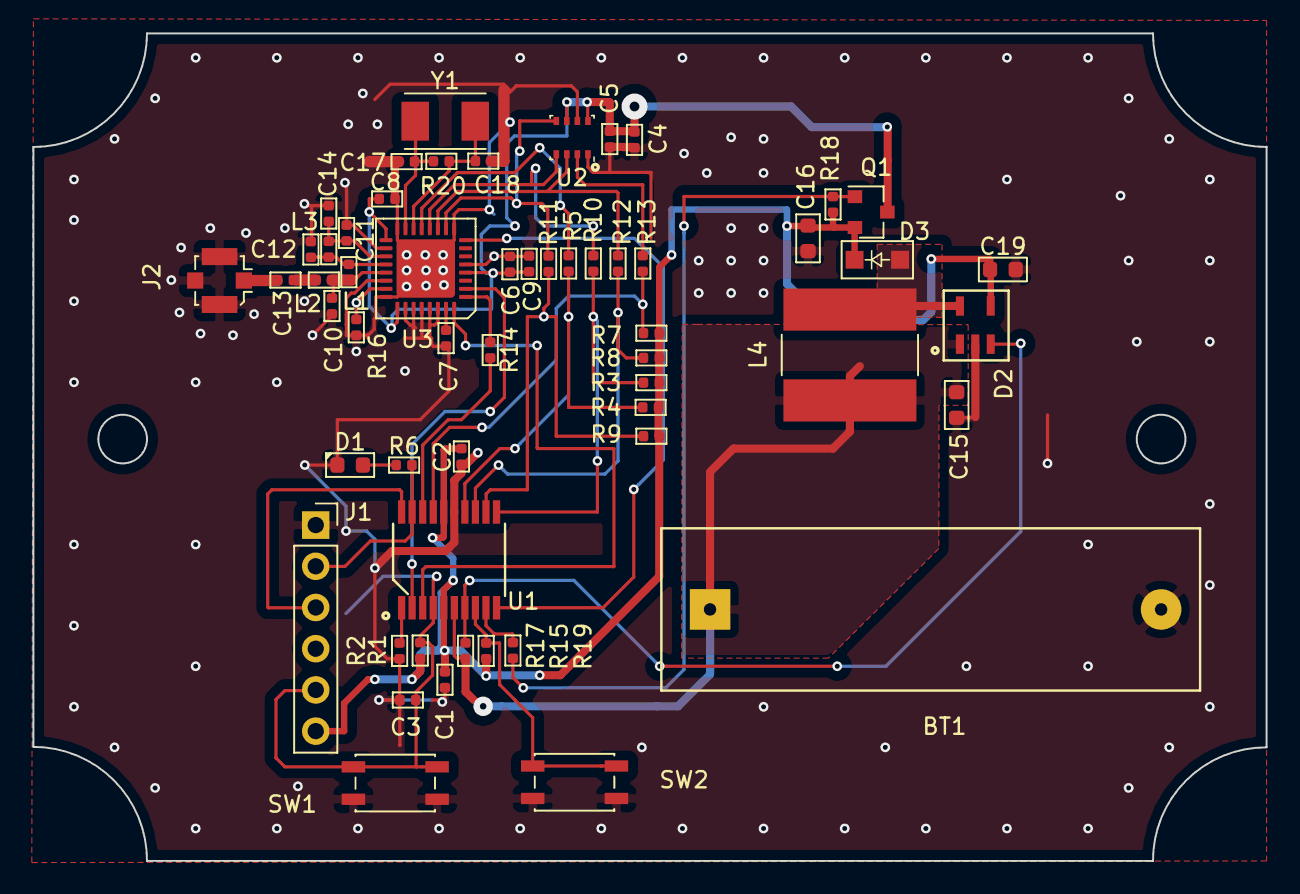
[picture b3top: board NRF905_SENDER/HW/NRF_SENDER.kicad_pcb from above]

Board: 2 copper layers, 76.0 x 51.0 mm, 56 parts (0 on the bottom side), 38 nets.

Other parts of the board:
C4: 0.1 uf; C_0402_1005Metric
C5: 4.7 uf; C_0402_1005Metric
U2: BME280; Bosch_LGA-8_2.5x2.5mm_P0.65mm_ClockwisePinNumbering

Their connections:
/CSK: U2.4; also elsewhere on the board
/CS_BME: U2.2; also elsewhere on the board
/MISO: U2.5; also elsewhere on the board
/MOSI: U2.3; also elsewhere on the board
/POWER/POWER_MODULES: C4.1, C5.1, U2.6, U2.8; also elsewhere on the board
GND: C4.2, C5.2, U2.1, U2.7; also elsewhere on the board
